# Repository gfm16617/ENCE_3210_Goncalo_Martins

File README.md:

# ENCE_3210_Goncalo_Martins

is this working...

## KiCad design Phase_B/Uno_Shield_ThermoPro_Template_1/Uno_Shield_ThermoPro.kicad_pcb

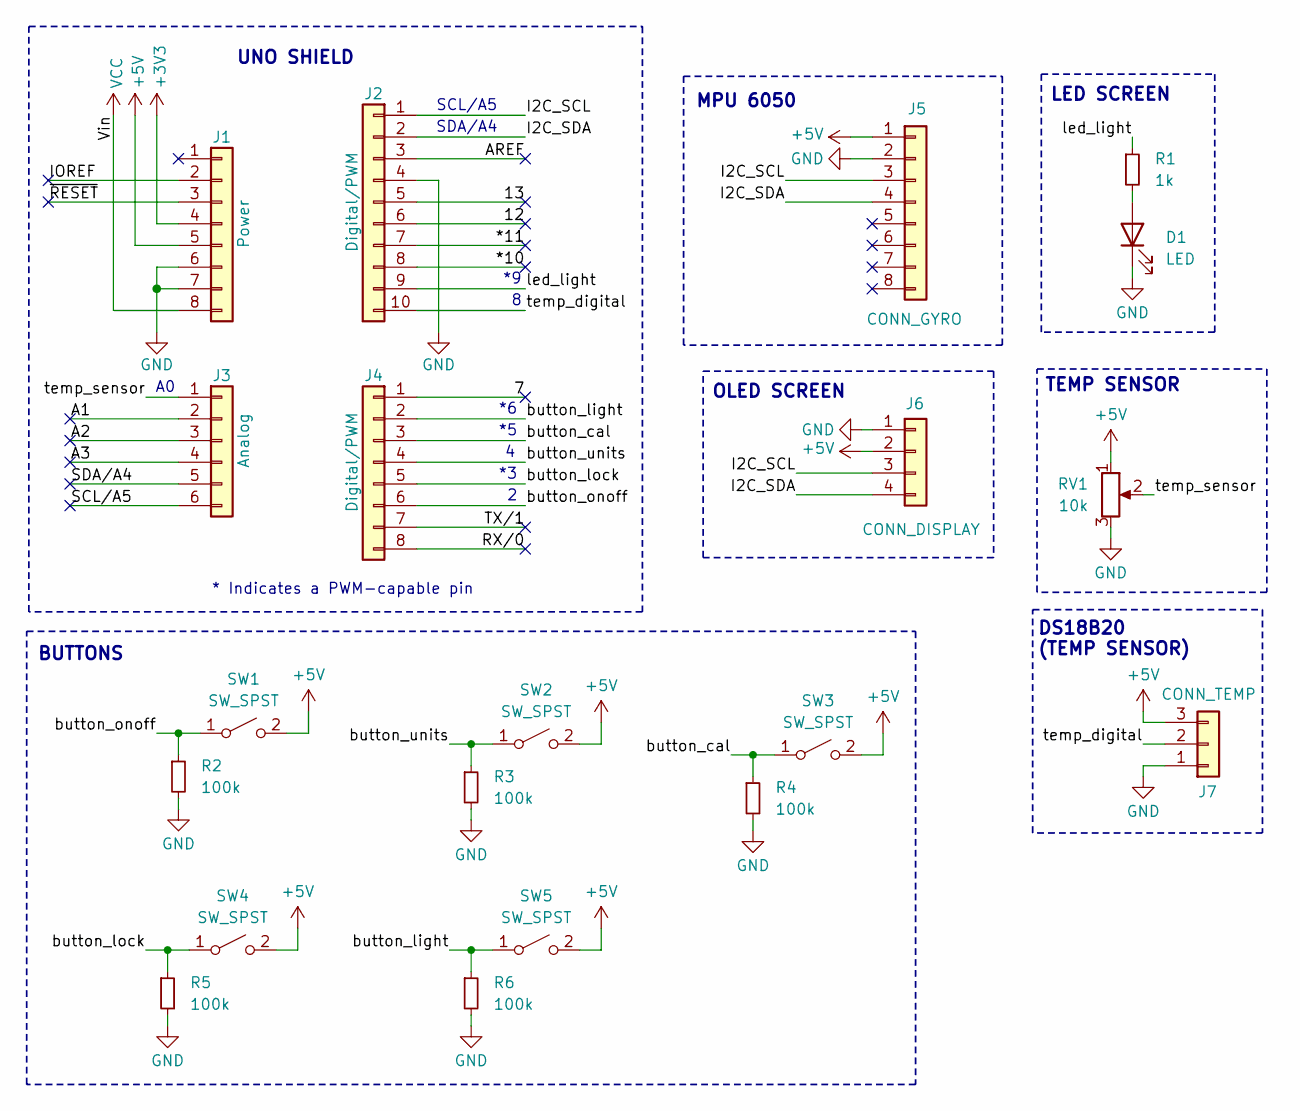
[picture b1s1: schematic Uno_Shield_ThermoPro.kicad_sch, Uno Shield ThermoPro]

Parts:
D1: LED; LED_D5.0mm
J1: Power; PinSocket_1x08_P2.54mm_Vertical
J2: Digital/PWM; PinSocket_1x10_P2.54mm_Vertical
J3: Analog; PinSocket_1x06_P2.54mm_Vertical
J4: Digital/PWM; PinSocket_1x08_P2.54mm_Vertical
J5: CONN_GYRO; PinSocket_1x08_P2.54mm_Vertical
J6: CONN_DISPLAY; PinSocket_1x04_P2.54mm_Vertical
J7: CONN_TEMP; JST_XH_B3B-XH-A_1x03_P2.50mm_Vertical
R1: 1k; R_Axial_DIN0207_L6.3mm_D2.5mm_P10.16mm_Horizontal
R2, R3, R4, R5, R6: 100k; R_Axial_DIN0207_L6.3mm_D2.5mm_P10.16mm_Horizontal
RV1: 10k; Potentiometer_Bourns_3386P_Vertical
SW1, SW2, SW3, SW4, SW5: SW_SPST; SW_PUSH_6mm

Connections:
+3V3: J1.4
+5V: J1.5, J5.1, J6.2, J7.3, RV1.1, SW1.2 (B), SW2.2 (B), SW3.2 (B), SW4.2 (B), SW5.2 (B)
/7: J4.1
/12: J2.6
/13: J2.5
/*10: J2.8
/*11: J2.7
/A1: J3.2
/A2: J3.3
/A3: J3.4
/AREF: J2.3
/I2C_SCL: J2.1, J5.3, J6.3
/I2C_SDA: J2.2, J5.4, J6.4
/IOREF: J1.2
/RX/0: J4.8
/SCL/A5: J3.6
/SDA/A4: J3.5
/TX/1: J4.7
/button_cal: J4.3, R4.1, SW3.1 (A)
/button_light: J4.2, R6.1, SW5.1 (A)
/button_lock: J4.5, R5.1, SW4.1 (A)
/button_onoff: J4.6, R2.1, SW1.1 (A)
/button_units: J4.4, R3.1, SW2.1 (A)
/led_light: J2.9, R1.1
/temp_digital: J2.10, J7.2
/temp_sensor: J3.1, RV1.2
/~RESET: J1.3
GND: D1.1 (K), J1.6, J1.7, J2.4, J5.2, J6.1, J7.1, R2.2, R3.2, R4.2, R5.2, R6.2, RV1.3
unnamed: D1.2 (A), R1.2
VCC: J1.8

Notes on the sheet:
DS18B20 (TEMP SENSOR)
OLED SCREEN
LED SCREEN
TEMP SENSOR
UNO SHIELD
MPU 6050
SCL/A5
SDA/A4
BUTTONS
* Indicates a PWM-capable pin

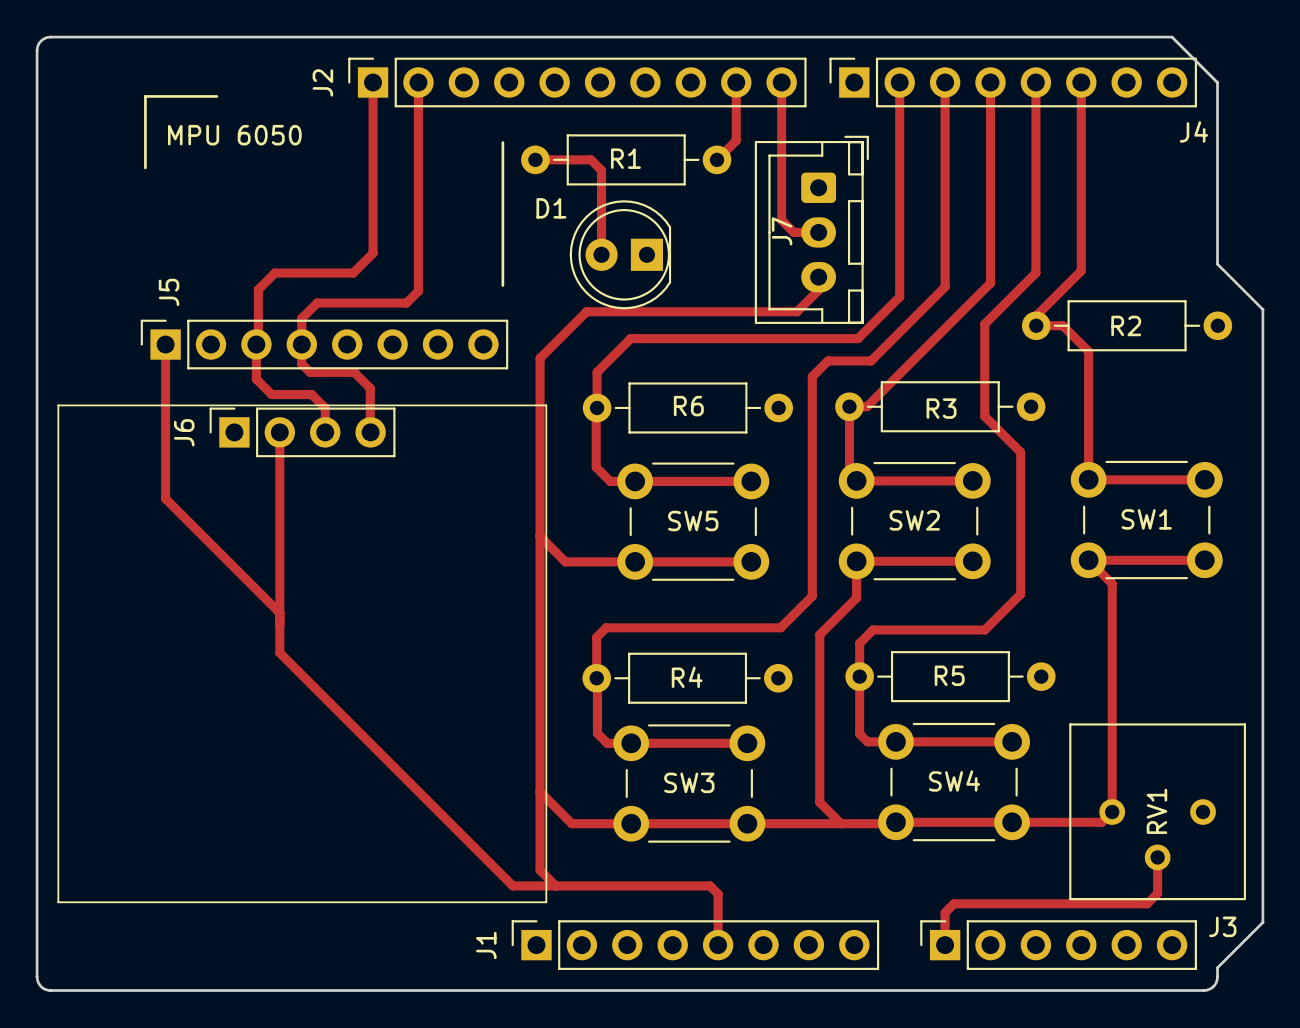
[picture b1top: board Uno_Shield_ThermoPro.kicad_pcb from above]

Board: 2 copper layers, 68.6 x 53.3 mm, 20 parts (0 on the bottom side), 13 nets.

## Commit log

2025-01-10 bla bla
2025-01-10 djfkghdalfghadlfkd
2025-01-31 Phase B
2025-01-31 delete
